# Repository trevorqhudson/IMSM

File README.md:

# IMSM
integrated multi-sensor module (IMSM) for transducing flow dynamics in hydrocephalic shunts

This repo contains firmware + schematics for a portable datalogger designed for an prototype polymer sensor device.

### Features: ###
* IMSM thermal flow sensor, bubble pressure sensor, and substrate/electrode integrity sensors using AD5933 LCR IC
* Low-side current sensing thru flow sensor heater 
* Sensirion LD20 flow sensor (I2C)
* EIS/CV sweeps addressable to any of 4 measurement electrode pairs + electrolysis electrodes
* Extends frequency range of AD5933 both low and high w/ external clock (code incomplete, but tapeout done)
* Completely autonomous data collection - designed for clinician use, not for researchers only
* Low-power + sleep mode extends battery life

[Meng Lab research page](https://biomems.usc.edu/ "easter egg text")

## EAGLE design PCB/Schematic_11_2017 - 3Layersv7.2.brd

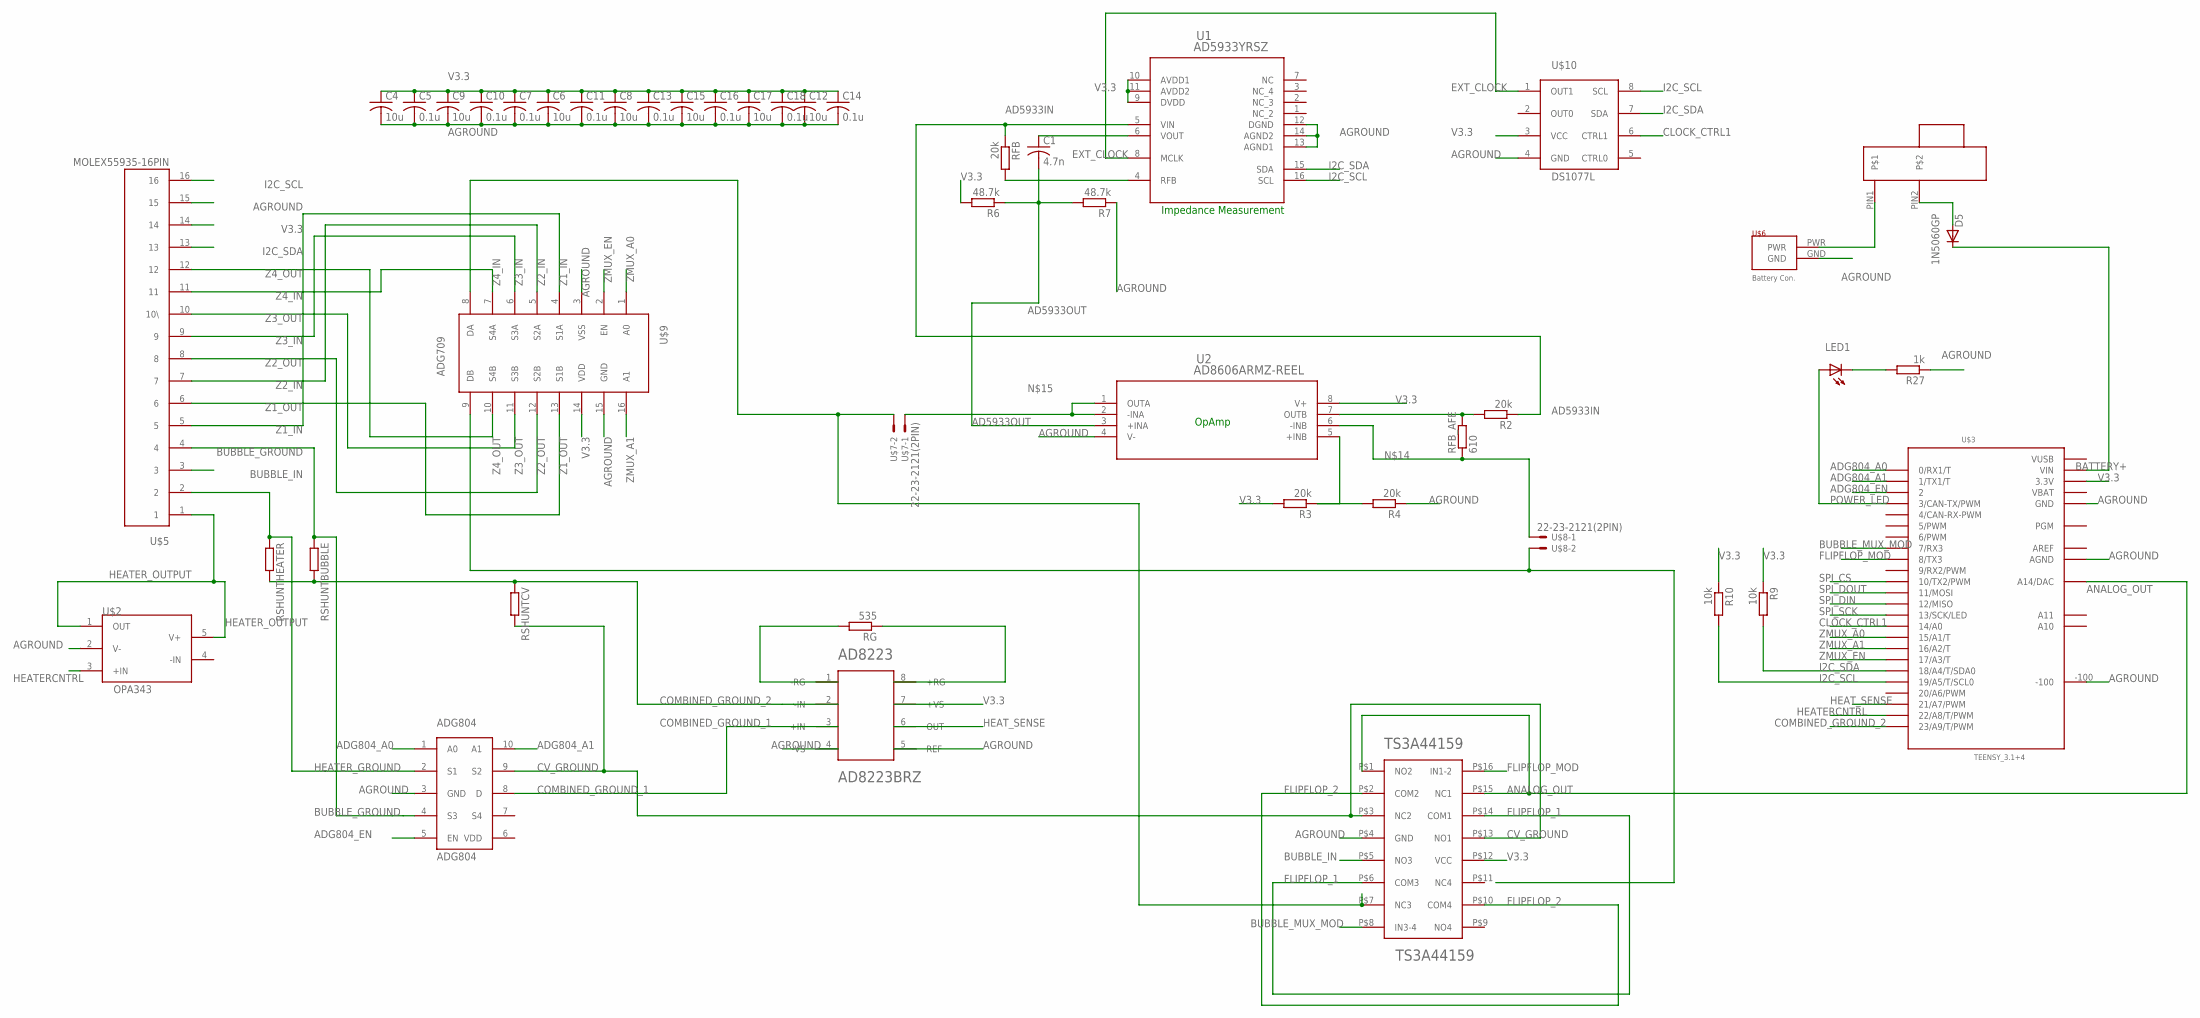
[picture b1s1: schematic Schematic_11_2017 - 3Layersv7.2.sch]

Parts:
ADG804: ADG804; MSOP10
C1: 4.7n; C1206
C4, C6, C8, C9, C12, C15, C17: 10u; C1206
C5, C7, C10, C11, C13, C14, C16, C18: 0.1u; C1206
D5: 1N5060GP; DO15-12
LED1: LED_ELD260; LED_LD260
R2, R3, R4: 20k; R1206
R6, R7: 48.7k; R1206
R9, R10: 10k; R1206
R27: 1k; R1206
RFB: 20k; R1206
RFB_AFE: 610; R1206
RG: 535; R1206
RSHUNTBUBBLE: RR1206; R1206
RSHUNTCV: RR1206; R1206
RSHUNTHEATER: RR1206; R1206
TS3A44159: TS3A44159; TSSOP16
U1: AD5933YRSZ; RS_16
U2: AD8606ARMZ-REEL; RM_8
U$1: AD8223BRZ; R-8
U$2: OPA343; SOT95P280X145-5N
U$3: TEENSY_3.1+4
U$4: C&KSWITCH; 2POS_SWITCH
U$5: MOLEX55935-16PIN
U$6: PH_2PIN; JST_PH_2PIN
U$7, U$8: 22-23-2121(2PIN)
U$9: ADG709; TSSOP16
U$10: DS1077L; SO08

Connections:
AD5933IN: R2.1, RFB.1, U1.5 (VIN)
AD5933OUT: C1.2, R6.1, R7.2, U2.3 (+INA)
ADG804_A0: ADG804.1 (A0), U$3.0 (0/RX1/T)
ADG804_A1: ADG804.10 (A1), U$3.1 (1/TX1/T)
ADG804_EN: ADG804.5 (EN), U$3.2
AGROUND: ADG804.3 (GND), C4.2, C5.2, C6.2, C7.2, C8.2, C9.2, C10.2, C11.2, C12.2, C13.2, C14.2, C15.2, C16.2, C17.2, C18.2, R4.1, R7.1, R27.1, TS3A44159.P$4 (GND), U1.12 (DGND), U1.13 (AGND1), U1.14 (AGND2), U2.4 (V-), U$1.4 (-VS), U$1.5 (REF), U$2.2 (V-), U$3.-100, U$3.AGND, U$3.GND1 (GND), U$5.15, U$6.GND, U$9.3 (VSS), U$9.15 (GND), U$10.4 (GND)
ANALOG_OUT: TS3A44159.P$1 (NO2), TS3A44159.P$15 (NC1), U$3.A14 (A14/DAC)
AREF: U$3.AREF
BATTERY+: D5.C, U$3.VIN
BUBBLE_GROUND: ADG804.4 (S3), RSHUNTBUBBLE.1, U$5.4
BUBBLE_IN: TS3A44159.P$5 (NO3), U$5.3
BUBBLE_MUX_MOD: TS3A44159.P$8 (IN3-4), U$3.7 (7/RX3)
CLOCK_CTRL1: U$3.14/A0, U$10.6 (CTRL1)
COMBINED_GROUND_1: ADG804.8 (D), U$1.3 (+IN)
COMBINED_GROUND_2: RSHUNTBUBBLE.2, RSHUNTCV.1, RSHUNTHEATER.2, U$1.2 (-IN), U$3.23/A9 (23/A9/T/PWM)
CV_GROUND: ADG804.9 (S2), RSHUNTCV.2, TS3A44159.P$3 (NC2), TS3A44159.P$13 (NO1)
EXT_CLOCK: U1.8 (MCLK), U$10.1 (OUT1)
FLIPFLOP_1: TS3A44159.P$6 (COM3), TS3A44159.P$14 (COM1)
FLIPFLOP_2: TS3A44159.P$2 (COM2), TS3A44159.P$10 (COM4)
FLIPFLOP_MOD: TS3A44159.P$16 (IN1-2), U$3.8 (8/TX3)
HEATERCNTRL: U$2.3 (+IN), U$3.22/A8 (22/A8/T/PWM)
HEATER_GROUND: ADG804.2 (S1), RSHUNTHEATER.1, U$5.2
HEATER_OUTPUT: U$2.1 (OUT), U$2.5 (V+), U$5.1
HEAT_SENSE: U$1.6 (OUT), U$3.21/A7 (21/A7/PWM)
I2C_SCL: R10.2, U1.16 (SCL), U$3.19/A5 (19/A5/T/SCL0), U$5.16, U$10.8 (SCL)
I2C_SDA: R9.2, U1.15 (SDA), U$3.18/A4 (18/A4/T/SDA0), U$5.13, U$10.7 (SDA)
unnamed: U$4.PIN1, U$6.PWR
unnamed: D5.A, U$4.PIN2
unnamed: RFB.2, U1.4 (RFB)
unnamed: LED1.K (C), R27.2
unnamed: C1.1, U1.6 (VOUT)
unnamed: R2.2, RFB_AFE.2, U2.7 (OUTB)
unnamed: R3.1, R4.2, U2.5 (+INB)
unnamed: RFB_AFE.1, U2.6 (-INB), U$8.1
unnamed: U2.1 (OUTA), U2.2 (-INA), U$7.1
unnamed: RG.2, U$1.1 (-RG)
unnamed: RG.1, U$1.8 (+RG)
POWER_LED: LED1.A, U$3.3 (3/CAN-TX/PWM)
SIGNAL+: TS3A44159.P$7 (NC3), U$7.2, U$9.8 (DA)
SIGNAL-: U$8.2, U$9.9 (DB)
SPI_CS: U$3.10 (10/TX2/PWM)
SPI_DIN: U$3.12 (12/MISO)
SPI_DOUT: U$3.11 (11/MOSI)
SPI_SCK: U$3.13 (13/SCK/LED)
V3.3: C4.1, C5.1, C6.1, C7.1, C8.1, C9.1, C10.1, C11.1, C12.1, C13.1, C14.1, C15.1, C16.1, C17.1, C18.1, R3.2, R6.2, R9.1, R10.1, TS3A44159.P$12 (VCC), U1.9 (DVDD), U1.10 (AVDD1), U1.11 (AVDD2), U2.8 (V+), U$1.7 (+VS), U$3.3.3V, U$3.3.3V1 (3.3V), U$5.14, U$9.14 (VDD), U$10.3 (VCC)
VBAT: U$3.VBAT
VUSB: U$3.VUSB
Z1_IN: U$5.5, U$9.4 (S1A)
Z1_OUT: U$5.6, U$9.13 (S1B)
Z2_IN: U$5.7, U$9.5 (S2A)
Z2_OUT: U$5.8, U$9.12 (S2B)
Z3_IN: U$5.9, U$9.6 (S3A)
Z3_OUT: U$5.10 (10\), U$9.11 (S3B)
Z4_IN: U$5.11, U$9.7 (S4A)
Z4_OUT: U$5.12, U$9.10 (S4B)
ZMUX_A0: U$3.15/A1 (15/A1/T), U$9.1 (A0)
ZMUX_A1: U$3.16/A2 (16/A2/T), U$9.16 (A1)
ZMUX_EN: U$3.17/A3 (17/A3/T), U$9.2 (EN)

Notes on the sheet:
Impedance Measurement
OpAmp

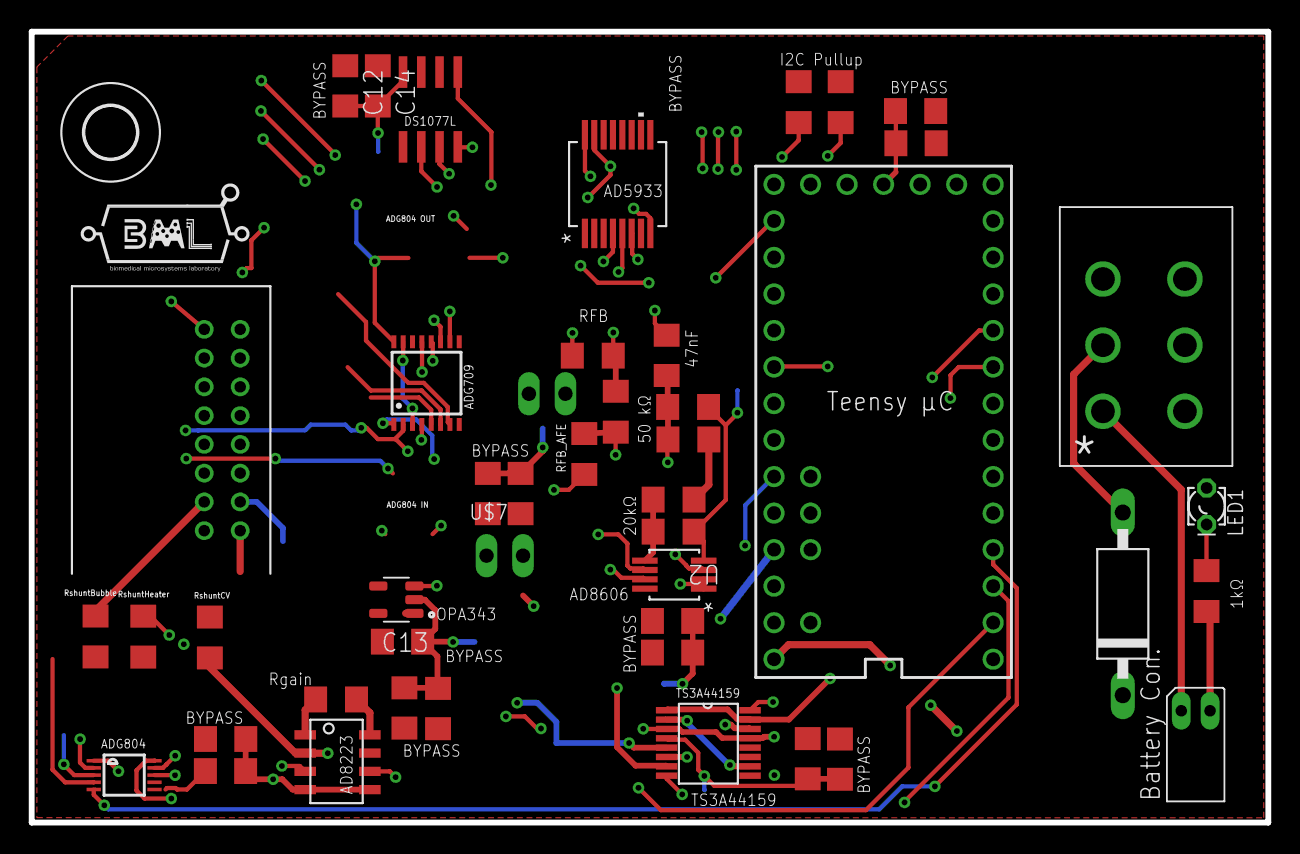
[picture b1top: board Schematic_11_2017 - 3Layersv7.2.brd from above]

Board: 4 copper layers, 86.0 x 55.0 mm, 47 parts (0 on the bottom side), 51 nets.

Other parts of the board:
H1: MOUNT-HOLE3.6; 3,6

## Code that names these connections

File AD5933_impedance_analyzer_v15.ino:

// changelog
// 5_22 - 6_6: gather user inputs as global variables, add time_comments option, eliminate phase flowchart for simple atan2 output, add sweep option, change PGA gain to x5,
//             comment out SD pins reset at start of setup()
// 6_7: reset 'time_now' in flow() before calling freqfunction() such that sampling rate is more predictable and consistent
// 6_9: slightly changed string definition in freqfunction(), added 'flow_timer' input to freqfunction(), moved pinMode declarations inside of flow(), changed all outputs pins to
//      digital - research how grounding a microcontroller works, is it standard practice to add pulldown resistors
// 6_22:snooze library, heater_on to user-controllable vars, set unused I/O pins to output
// 6_23:cleaning up sweep operations
// 6_26:snooze lib readded, manually code in sweep
// 6_27:finished manually coding in sweep, set real_ and imag_read to record on SD
// 6_28:start removing features until we find problem
// 7_26:save program parameters in SD write header
// 8_3: snocontinuing with saving parameters in SD write header, added cut-off check for fluidic short
// 8_4: add pressure sensing code
// 8_9: change LED to constantly on, add phase constants for patency sweep
// 8_10:change flow programming to make AD5933 calls smoother
// 9_6: add 'operand' variable to ease user changes to signal type, add sig figs to impedance displaygain
// 11_21: this version contains voltage measurement apparatus on analog read pins, in flow function
// v11.99: commented out all "Serial" references to try to save power. this should be the only change from v11.98
// v12: add sweepflag=o before all naked freqfunction calls, and follow by turning off AD5933 - otherwise, startup register sets won't happen
// v12.02: sent to CHLA on 3.27 - rename this version to change parameters
// v12.04: added bubble generation voltage
// v12.05: combining Priya's code for higher frequency measurement. removed delay
// v12.06: protocol for Alex
// v13:    rewriting all for PCB v2: temp sensing, LD20, portable CV, pressure ramp [switching architecture]
// v14:    new board update. ADG709 mux replaces CD4052 mux. new pin layouts. added DS1077L external crystal. changed low-side current sensing circuit.
// v14.2:  add PGA gain variation, 1x on exposed IDE and 5x on flow and covered IDE. covered IDE is still out of range here
// v14.3:  add EIS distinct function

#include <Wire.h>
#include <SD.h>
#include <SPI.h>
#include <math.h>
#include <Time.h>
#include <TimeLib.h>
#include <Snooze.h>
#include <SnoozeBlock.h>

//snooze
SnoozeAlarm alarm;
SnoozeBlock config1(alarm);


//user-controllable vars, in no particular order
const uint32_t heat_time = 10000;  //time heater is on in msecs (flow)
const uint32_t warmup_time = 10000;
const uint32_t cooldown_time = 60000;
const uint32_t total_time = heat_time + cooldown_time + warmup_time;
const int NC_time = 10000;  //time nuc core electrodes are active in msecs (pressure)l
//gain factors calibrated for a 610 gain resistor for Z_mux
const float gain_factor_1x = 5.9788E6;  //this could be calculated w/ auto calibration step (freqfunction)
const float gain_factor_intercept_1x = -42.82;
const float gain_factor_5x = 3.0360E6;  //this could be calculated w/ auto calibration step (freqfunction)
const float gain_factor_intercept_5x = -397.23;
const boolean time_comments = false;
const int sense_resolution = 200; // msecs between ad5933 calls
boolean heater_on = true;
const int sleep_hours = 0;
const int sleep_mins = 55; //measurement cycle as is takes 04:05 [m:s] to complete, so 55 mins, 55 secs = 1 start per hour
const int sleep_secs = 55;
boolean CV_direction = true; //true = positive voltage defined as transmit electrodes, false = positive voltage through return electrodes

//deeper user vars
//  uint32_t act_code1 = 0xB0;
//  uint32_t act_code2 = 0x10;
//  uint32_t act_code3 = 0x20;
uint8_t operand = B0001;  //control interrogation voltage and PGA gain; see AD5933 datasheet [0=5x, 1=1x]
const int settling_time = 300;

//freq sweep vars
const int num_increm = 17;  //number of freq increments. if you change this, change phase offset array in freqfunction()
unsigned long start_freq;
const unsigned long delta_freq = 5000;
int sweep_index = 0;  //0 is start frequency, 1 is start + delta frequency, etc
bool sweepflag = 0; //0 is first sweep, 1 is mid-sweep,  controls activating/powering down AD5933
unsigned long AD5933_freq = 16000000; //16 MHz internal oscillator

//global vars
const int dtime = 10;  //delay between I2C operations, in usecs
const int CS = 4;  //pin select for CS
const float pi = 3.14159265;
boolean sweep_on = 0; //is  your measurement a frequency sweep or a single frequency?
const int AD5933ADDR = 0x0D;
uint16_t measure_number = 0;
int heat_voltage; //heater voltage sense
const float V_power = 3300; //[mB], PCB positive supply voltage
const float a_voltage_max = 4095; //12 bit resolution
const int DS1077LADDR = B1011000;

//sensirion LD20 vars
const int LD20_address = 8;
int ret;
float calibration_factor = 0.9; //20(mL/hr)^-1 => 1.2(uL/min)^-1; should be around 1.2, but is diff for every sensor
uint16_t sensor_flow_value;
int16_t signed_flow_value;
float scaled_flow_value;
byte sensor_flow_crc;
uint16_t sensor_temp_value;
byte sensor_temp_crc;
uint16_t aux_value;
byte aux_crc;

//pin assignments
const int ADG804_A0 = 0;
const int ADG804_A1 = 1;
const int ADG804_EN = 2;

const int LED = 3;

const int bubblemux_mod = 7; //mux between 4 signal electrode pairs (LOW) OR bubble input (HIGH)
const int flipflop_mod = 8; //flipflop mux between analog out as ch.1 and heater grond as ch.2 (LOW), or heater ground as ch.1 and analog out as ch.2 (HIGH)

const int CLOCK_CTRL1 = 14;
const int ZMUX_A0 = 15;
const int ZMUX_A1 = 16;
const int ZMUX_EN = 17;

const int heat_sense = 21;
const int heatercntrl = 22;
const int ground = 23;
const int analog_out = A14;

int myregister = 0;
int myregisterval = 0;

int measurement_index;  //tracks number of ad5933 calls

int global_imp_mag;


time_t getTeensy3Time() {
  return Teensy3Clock.get();
}


void setup() {
  Wire.begin();
  Serial.begin(9600);

  //  Serial.println("take3");

  //snooze stuff
  alarm.setRtcTimer(sleep_hours, sleep_mins, sleep_secs);

  //prepare analog output pin
  analogWriteResolution(12);
  analogWrite(analog_out, 0);

  //initialize SD card and make a file
  if (!SD.begin(CS)) {
    Serial.println("Card failed to read");
    return;
  }
  Serial.println("Card initialized");

  setSyncProvider(getTeensy3Time);

  //ground ground pin
  pinMode(ground, OUTPUT);
  digitalWrite(ground, LOW);

  //set unused I/O pins to OUTPUT to save power
  pinMode(0, OUTPUT); pinMode(1, OUTPUT); pinMode(2, OUTPUT); pinMode(5, OUTPUT); pinMode(6, OUTPUT);
  pinMode(10, OUTPUT); pinMode(11, OUTPUT); pinMode(12, OUTPUT); pinMode(13, OUTPUT); //pinMode(17, OUTPUT);

  //  Serial.end(); // shut off USB

  pinMode(LED, OUTPUT);      //turn on LED all the time
  digitalWrite(LED, HIGH);

  // Set all pinModes here for speed - none should change during program

  //talk to mux
  pinMode(ZMUX_A0, OUTPUT);  //corresponds to mux logic A
  pinMode(ZMUX_A1, OUTPUT);  //logic B
  pinMode(ZMUX_EN, OUTPUT);

  pinMode(heatercntrl, OUTPUT);

  pinMode(bubblemux_mod, OUTPUT);
  pinMode(flipflop_mod, OUTPUT);

  pinMode(heat_sense, INPUT);

  pinMode(CLOCK_CTRL1, OUTPUT);

  //default + safe switching mode is: flipflop=unflipped, bubble mux=bubble circuit(to isolate signal lines), R_shunt=low R
  digitalWrite(bubblemux_mod, HIGH);
  digitalWrite(flipflop_mod, LOW);

  digitalWrite(ADG804_EN, HIGH); //default open shunt resistor mux

  digitalWrite(CLOCK_CTRL1, HIGH); //default power down DS1077L

  delay(3000);  //time to write new program
}

void loop() {
  main1();
  measure_number++;

  delay(2000);  //don't remove this or snooze will crash

  Snooze.deepSleep(config1);
}



/////////////////////////////////////////////////////////////////////////////////////////////////////////////////////////////////////////////////////////////////////////////////

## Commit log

2017-03-30 Create main
2017-03-30 Update main
2017-05-23 Create main2
2017-05-23 Create gittest
2017-05-23 Update gittest
2021-05-16 Rename AD5933_impedance_analyzer_v15.ino to Firmware/AD5933_impedance_analyzer_v15.ino
2021-05-16 Rename CV_sweep.ino to Firmware/CV_sweep.ino
2021-05-16 Rename EIS_sweep.ino to Firmware/EIS_sweep.ino
2021-05-16 Rename LD20_flow.ino to Firmware/LD20_flow.ino
2021-05-16 Rename flow.ino to Firmware/flow.ino
2021-05-16 Rename freqfunction.ino to Firmware/freqfunction.ino
2021-05-16 Rename main1.ino to Firmware/main1.ino
2021-05-16 Rename pressure.ino to Firmware/pressure.ino
2021-05-16 Rename wirewriteloop.ino to Firmware/wirewriteloop.ino
2021-05-16 Rename writeSD.ino to Firmware/writeSD.ino
2021-05-16 Create test
2021-05-17 Create tets
